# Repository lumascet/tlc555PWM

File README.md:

# TLC555 simple PWM controller

A very simple schematic for an analog PWM generator using the TLC555 IC. Intended for PWM fan control use.

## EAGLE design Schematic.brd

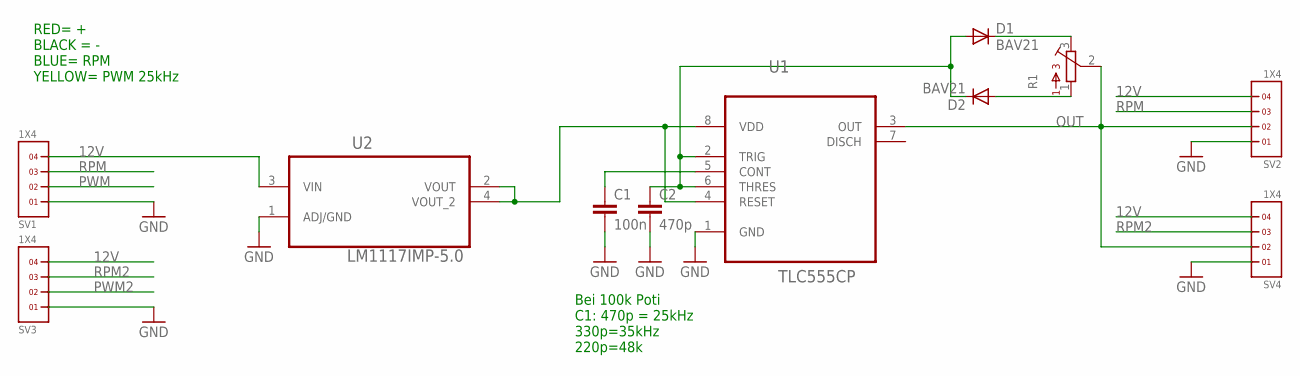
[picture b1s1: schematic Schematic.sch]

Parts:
C1: 100n; C025-025X050
C2: 470p; C025-025X050
D1, D2: BAV21; DO35-10
R1: 3362P
SV1, SV2, SV3, SV4: 1X4
U1: TLC555CP; DIP254P762X508-8
U2: LM1117IMP-5.0; SOT230P696X180-4N

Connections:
12V: SV1.4, SV2.4, SV3.4, SV4.4, U2.3 (VIN)
GND: C1.2, C2.2, SV1.1, SV2.1, SV3.1, SV4.1, U1.1 (GND), U2.1 (ADJ/GND)
unnamed: C2.1, D1.A, D2.C, U1.2 (TRIG), U1.6 (THRES)
unnamed: C1.1, U1.5 (CONT)
unnamed: D2.A, R1.1
unnamed: D1.C, R1.3
OUT: R1.2, SV2.2, SV4.2, U1.3 (OUT)
PWM: SV1.2
PWM2: SV3.2
RPM: SV1.3, SV2.3
RPM2: SV3.3, SV4.3
VDD: U1.4 (RESET), U1.8 (VDD), U2.2 (VOUT), U2.4 (VOUT_2)

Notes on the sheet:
RED= + BLACK = - BLUE= RPM YELLOW= PWM 25kHz
Bei 100k Poti C1: 470p = 25kHz 330p=35kHz 220p=48k

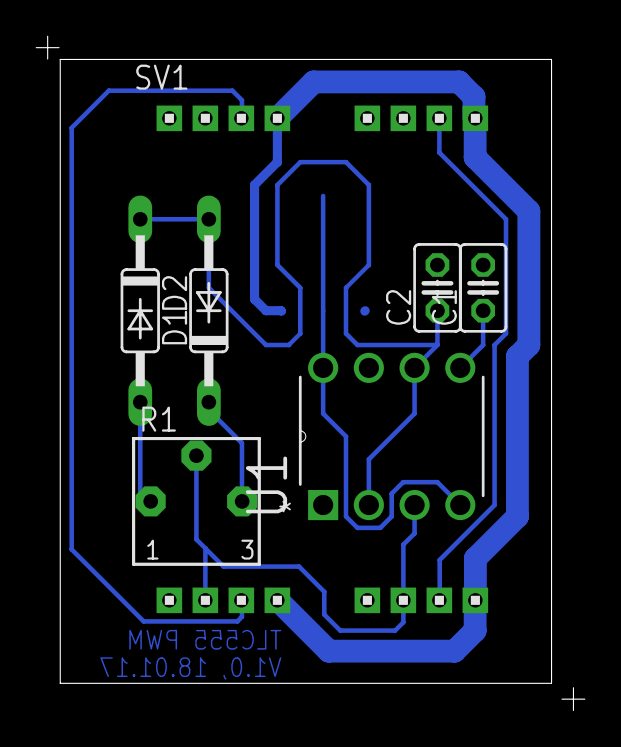
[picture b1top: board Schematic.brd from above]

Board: 2 copper layers, 27.3 x 34.7 mm, 11 parts (1 on the bottom side), 10 nets.
